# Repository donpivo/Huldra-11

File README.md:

Description: https://retronics.no/tag/huldra11/

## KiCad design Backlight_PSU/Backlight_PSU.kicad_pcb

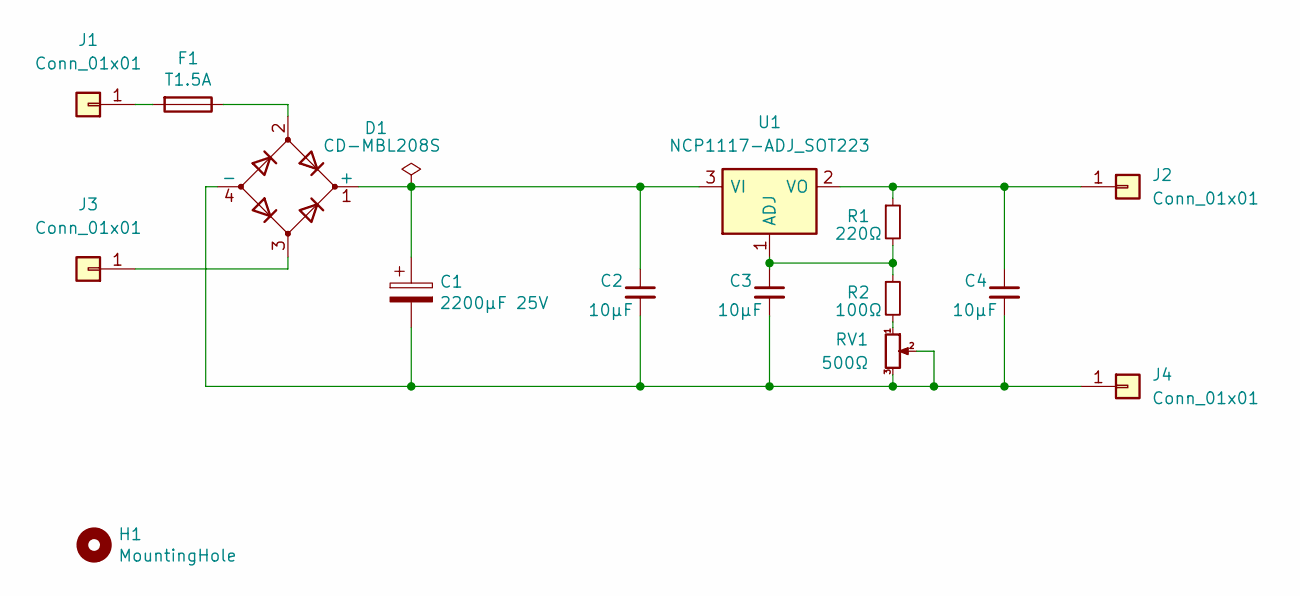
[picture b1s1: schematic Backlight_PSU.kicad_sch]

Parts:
C1: 2200µF 25V; CP_Elec_16x17.5
C2, C3, C4: 10µF; C_0603_1608Metric_Pad1.08x0.95mm_HandSolder
D1: CD-MBL208S; CDMBL208S
F1: T1.5A; Fuse_1206_3216Metric_Pad1.42x1.75mm_HandSolder
H1: MountingHole; MountingHole_3.7mm
J1, J2, J3, J4: Conn_01x01; TestPoint_Pad_2.5x2.5mm
R1: 220Ω; R_0603_1608Metric_Pad0.98x0.95mm_HandSolder
R2: 100Ω; R_0603_1608Metric_Pad0.98x0.95mm_HandSolder
RV1: 500Ω; Potentiometer_Bourns_TC33X_Vertical
U1: NCP1117-ADJ_SOT223; SOT-223-3_TabPin2

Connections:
unnamed: C1.1, C2.1, D1.1 (+), U1.3 (VI)
unnamed: C1.2, C2.2, C3.2, C4.2, D1.4 (-), J4.1, RV1.2, RV1.3
unnamed: D1.2, F1.1
unnamed: F1.2, J1.1
unnamed: C4.1, J2.1, R1.1, U1.2 (VO)
unnamed: D1.3, J3.1
unnamed: R2.2, RV1.1
unnamed: C3.1, R1.2, R2.1, U1.1 (ADJ)

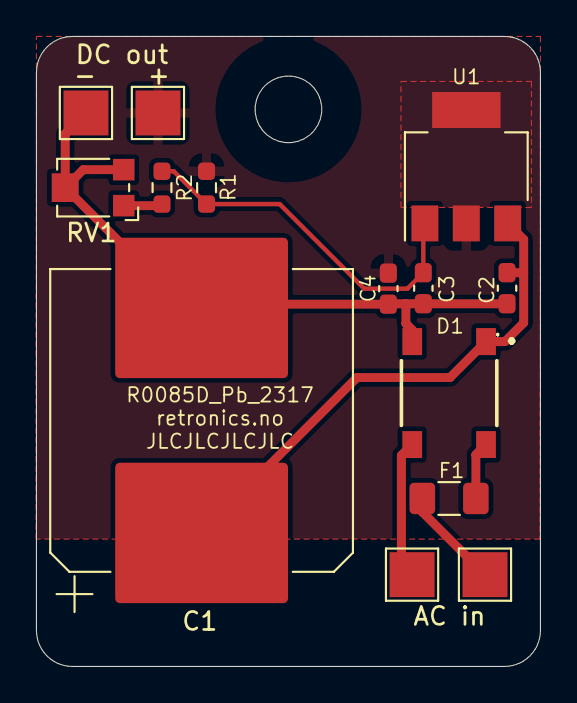
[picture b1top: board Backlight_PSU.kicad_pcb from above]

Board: 2 copper layers, 28.0 x 35.0 mm, 15 parts (0 on the bottom side), 8 nets.

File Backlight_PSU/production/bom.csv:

Designator,Footprint,Quantity,Value,LCSC Part #
C1,CP_Elec_16x17.5,1,2200µF 25V,
"C2, C3, C4",0603,3,10µF,
D1,CDMBL208S,1,CD-MBL208S,
F1,1206,1,T1.5A,
H1,MountingHole_3.7mm,1,MountingHole,
"J1, J2, J3, J4",TestPoint_Pad_2.5x2.5mm,4,Conn_01x01,
R1,0603,1,220Ω,
R2,0603,1,100Ω,
RV1,Potentiometer_Bourns_TC33X_Vertical,1,500Ω,
U1,SOT-223-3_TabPin2,1,NCP1117-ADJ_SOT223,

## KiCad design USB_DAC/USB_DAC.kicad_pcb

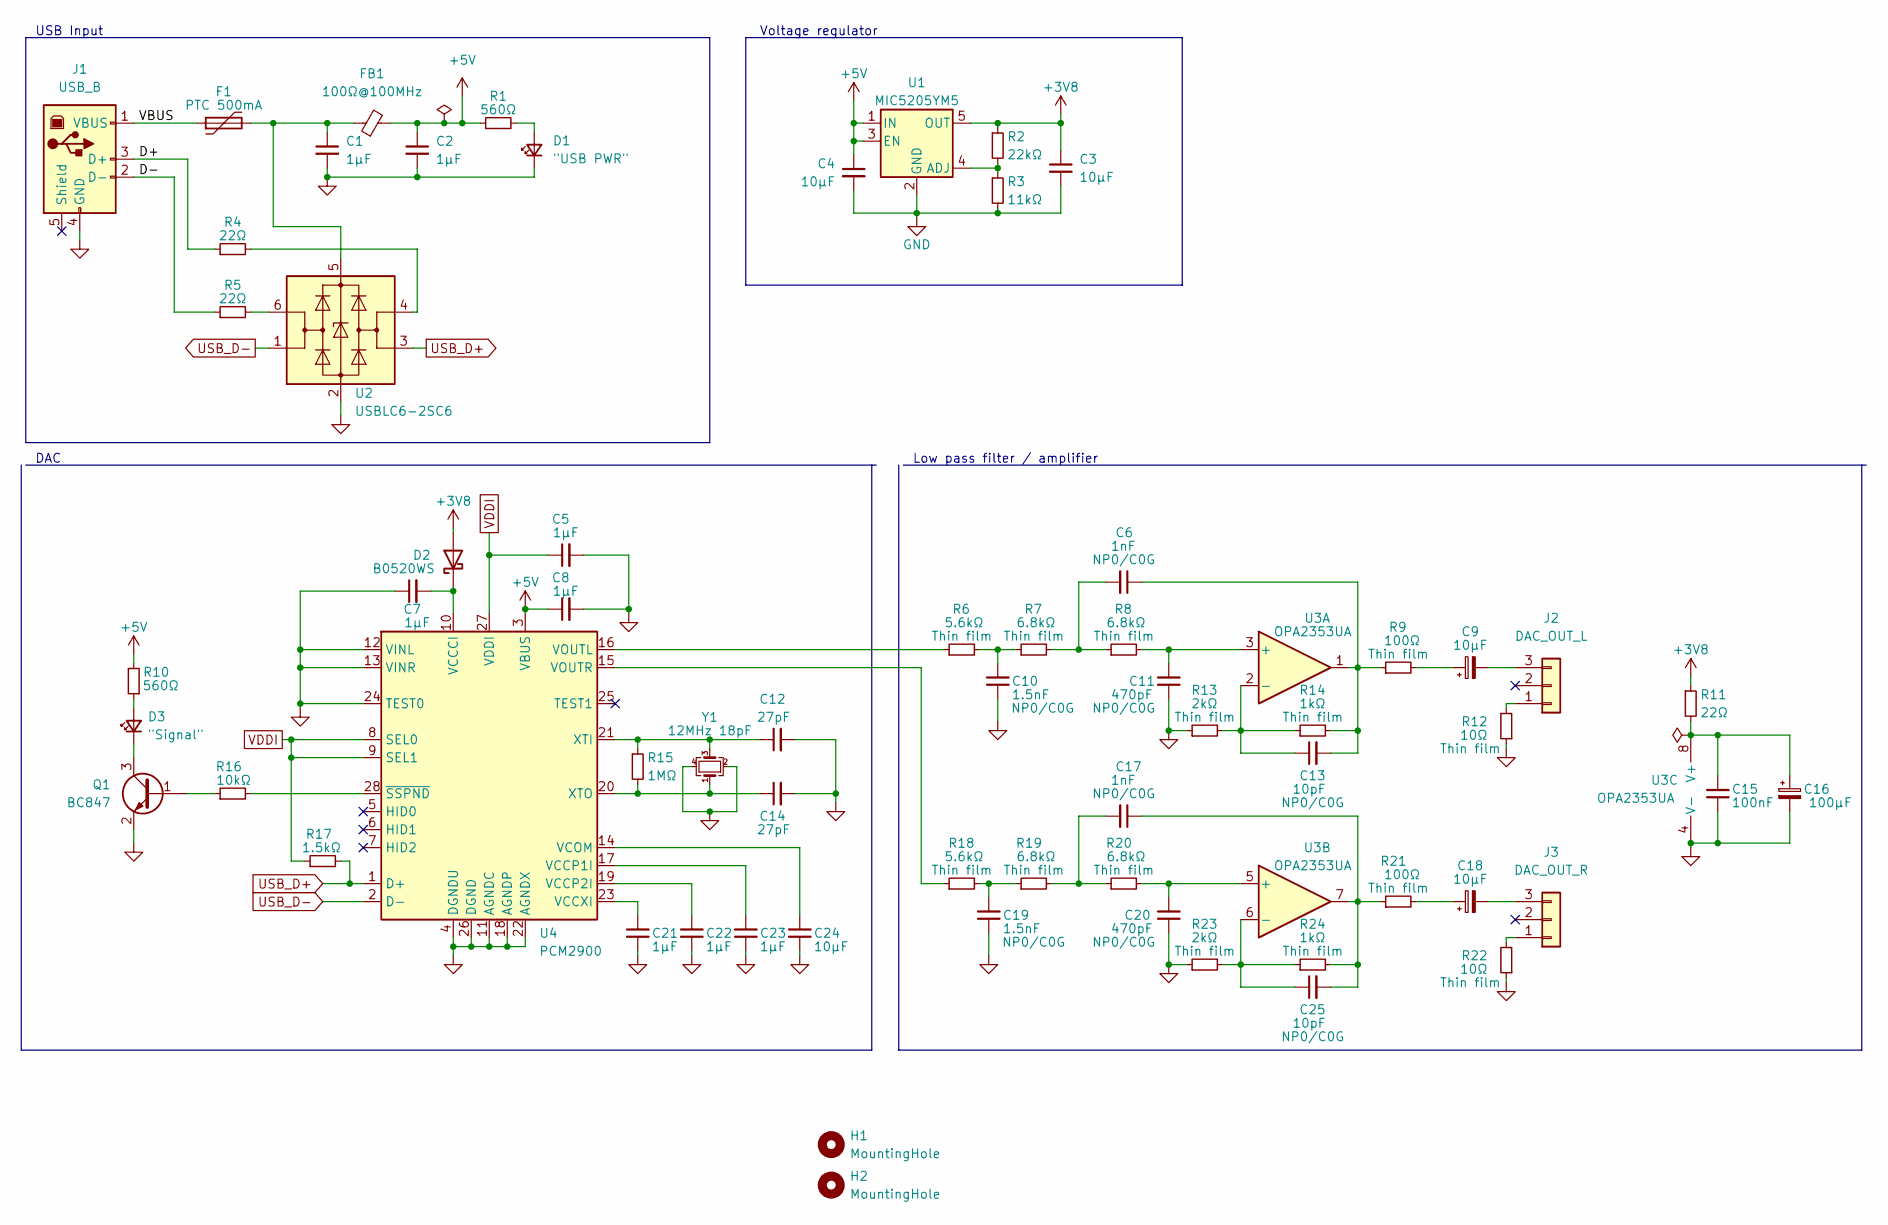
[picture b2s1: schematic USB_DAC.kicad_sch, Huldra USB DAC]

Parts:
C1, C2, C5, C7, C8, C21, C22, C23: 1µF; C_0603_1608Metric_Pad1.08x0.95mm_HandSolder
C3, C4, C24: 10µF; C_0603_1608Metric_Pad1.08x0.95mm_HandSolder
C6, C17: 1nF; C_0603_1608Metric_Pad1.08x0.95mm_HandSolder
C9, C18: 10µF; CP_Radial_D5.0mm_P2.00mm
C10, C19: 1.5nF; C_0603_1608Metric_Pad1.08x0.95mm_HandSolder
C11, C20: 470pF; C_0603_1608Metric_Pad1.08x0.95mm_HandSolder
C12, C14: 27pF; C_0603_1608Metric_Pad1.08x0.95mm_HandSolder
C13, C25: 10pF; C_0603_1608Metric_Pad1.08x0.95mm_HandSolder
C15: 100nF; C_0603_1608Metric_Pad1.08x0.95mm_HandSolder
C16: 100µF; CP_Radial_D5.0mm_P2.00mm
D1: "USB PWR"; LED_0603_1608Metric_Pad1.05x0.95mm_HandSolder
D2: B0520WS; D_SOD-323_HandSoldering
D3: "Signal"; LED_0603_1608Metric_Pad1.05x0.95mm_HandSolder
F1: PTC 500mA; Fuse_0805_2012Metric_Pad1.15x1.40mm_HandSolder
FB1: 100Ω@100MHz; L_0603_1608Metric_Pad1.05x0.95mm_HandSolder
H1, H2: MountingHole; MountingHole_3.2mm_M3
J1: USB_B; 292304
J2: DAC_OUT_L; KF2510-3P
J3: DAC_OUT_R; KF2510-3P
Q1: BC847; SOT-23
R1, R10: 560Ω; R_0603_1608Metric_Pad0.98x0.95mm_HandSolder
R2: 22kΩ; R_0603_1608Metric_Pad0.98x0.95mm_HandSolder
R3: 11kΩ; R_0603_1608Metric_Pad0.98x0.95mm_HandSolder
R4, R5, R11: 22Ω; R_0603_1608Metric_Pad0.98x0.95mm_HandSolder
R6, R18: 5.6kΩ; R_0603_1608Metric_Pad0.98x0.95mm_HandSolder
R7, R8, R19, R20: 6.8kΩ; R_0603_1608Metric_Pad0.98x0.95mm_HandSolder
R9, R21: 100Ω; R_0603_1608Metric_Pad0.98x0.95mm_HandSolder
R12, R22: 10Ω; R_0603_1608Metric_Pad0.98x0.95mm_HandSolder
R13, R23: 2kΩ; R_0603_1608Metric_Pad0.98x0.95mm_HandSolder
R14, R24: 1kΩ; R_0603_1608Metric_Pad0.98x0.95mm_HandSolder
R15: 1MΩ; R_0603_1608Metric_Pad0.98x0.95mm_HandSolder
R16: 10kΩ; R_0603_1608Metric_Pad0.98x0.95mm_HandSolder
R17: 1.5kΩ; R_0603_1608Metric_Pad0.98x0.95mm_HandSolder
U1: MIC5205YM5; SOT-23-5
U2: USBLC6-2SC6; SOT-23-6
U3: OPA2353UA; SOIC-8_3.9x4.9mm_P1.27mm
U4: PCM2900; SSOP-28_5.3x10.2mm_P0.65mm
Y1: 12MHz 18pF; Crystal_SMD_3225-4Pin_3.2x2.5mm_HandSoldering

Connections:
+3V8: C3.1, D2.2 (A), R2.1, R11.1, U1.5 (OUT)
+5V: C2.1, C4.1, C8.1, FB1.2, R1.1, R10.2, U1.1 (IN), U1.3 (EN), U4.3 (VBUS)
/D+: J1.3 (D+), R4.1
/D-: J1.2 (D-), R5.1
/VBUS: F1.1, J1.1 (VBUS)
GND: C1.2, C2.2, C3.2, C4.2, C5.2, C7.1, C8.2, C10.1, C11.1, C12.2, C14.2, C15.1, C16.2, C19.1, C20.1, C21.1, C22.1, C23.1, C24.1, D1.1 (K), J1.4 (GND), Q1.2 (E), R3.2, R12.1, R13.1, R22.1, R23.1, U1.2 (GND), U2.2 (GND), U3.4 (V-), U4.4 (DGNDU), U4.11 (AGNDC), U4.12 (VINL), U4.13 (VINR), U4.18 (AGNDP), U4.22 (AGNDX), U4.24 (TEST0), U4.26 (DGND), Y1.2, Y1.4
unnamed: C6.2, R7.2, R8.1
unnamed: C9.1, R9.2
unnamed: C10.2, R6.2, R7.1
unnamed: C6.1, C13.2, R9.1, R14.2, U3.1
unnamed: C17.1, C25.2, R21.1, R24.2, U3.7
unnamed: C17.2, R19.2, R20.1
unnamed: C18.1, R21.2
unnamed: C19.2, R18.2, R19.1
unnamed: D1.2 (A), R1.2
unnamed: C7.2, D2.1 (K), U4.10 (VCCCI)
unnamed: D3.2 (A), R10.1
unnamed: D3.1 (K), Q1.3 (C)
unnamed: J2.1, R12.2
unnamed: C9.2, J2.3
unnamed: J3.1, R22.2
unnamed: C18.2, J3.3
unnamed: Q1.1 (B), R16.1
unnamed: R4.2, U2.4 (I/O2)
unnamed: R5.2, U2.6 (I/O1)
unnamed: R2.2, R3.1, U1.4 (ADJ)
unnamed: C1.1, F1.2, FB1.1, U2.5 (VBUS)
unnamed: C11.2, R8.2, U3.3 (+)
unnamed: C13.1, R13.2, R14.1, U3.2 (-)
unnamed: C20.2, R20.2, U3.5 (+)
unnamed: C25.1, R23.2, R24.1, U3.6 (-)
unnamed: C15.2, C16.1, R11.2, U3.8 (V+)
unnamed: C23.2, U4.17 (VCCP1I)
unnamed: C22.2, U4.19 (VCCP2I)
unnamed: C21.2, U4.23 (VCCXI)
unnamed: C24.2, U4.14 (VCOM)
unnamed: R6.1, U4.16 (VOUTL)
unnamed: R18.1, U4.15 (VOUTR)
unnamed: C12.1, R15.1, U4.21 (XTI), Y1.3
unnamed: C14.1, R15.2, U4.20 (XTO), Y1.1
unnamed: R16.2, U4.28 (~SSPND)
USB_D+: R17.2, U2.3 (I/O2), U4.1 (D+)
USB_D-: U2.1 (I/O1), U4.2 (D-)
VDDI: C5.1, R17.1, U4.8 (SEL0), U4.9 (SEL1), U4.27 (VDDI)

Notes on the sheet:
Voltage regulator
Low pass filter / amplifier
DAC
USB Input

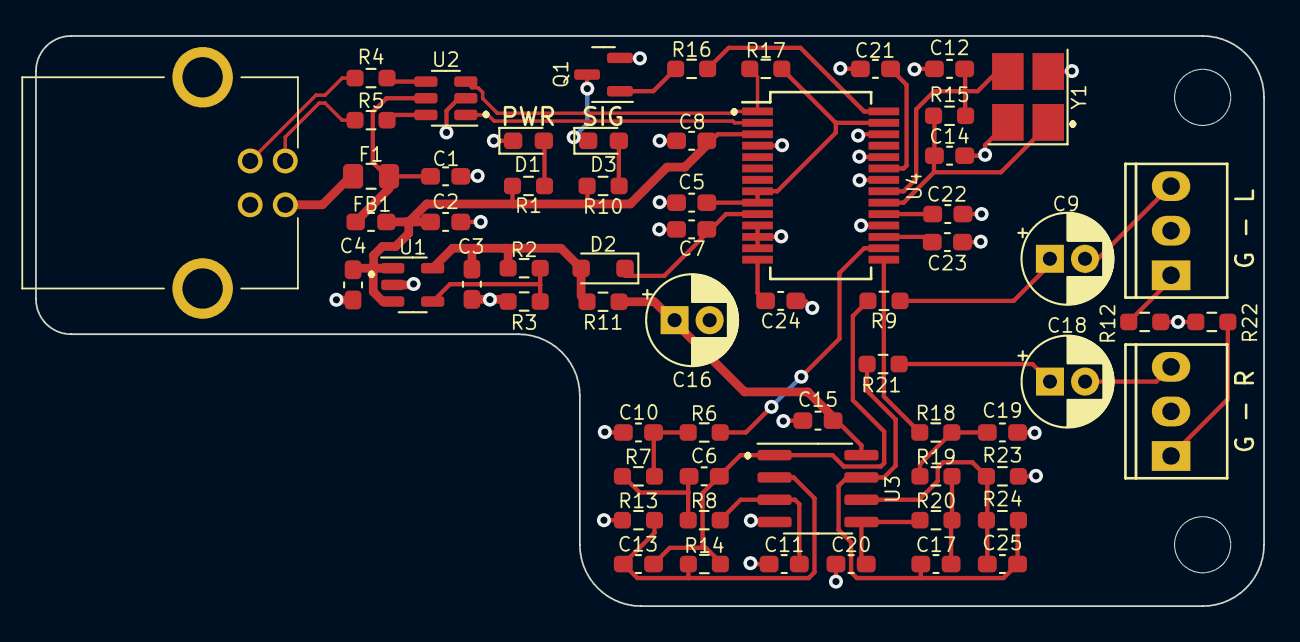
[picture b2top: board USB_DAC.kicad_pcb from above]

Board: 2 copper layers, 70.0 x 32.5 mm, 65 parts (0 on the bottom side), 44 nets.

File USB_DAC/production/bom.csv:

Designator,Footprint,Quantity,Value,LCSC Part #
"C1, C2, C21, C22, C23, C5, C7, C8",0603,8,1µF,
"C10, C19",0603,2,1.5nF,
"C11, C20",0603,2,470pF,
"C12, C14",0603,2,27pF,
"C13, C25",0603,2,10pF,
C15,0603,1,100nF,
C16,CP_Radial_D5.0mm_P2.00mm,1,100µF,
"C17, C6",0603,2,1nF,
"C18, C9",CP_Radial_D5.0mm_P2.00mm,2,10µF,
"C24, C3, C4",0603,3,10µF,
D1,0603,1,"""USB PWR""",
D2,D_SOD-323_HandSoldering,1,B0520WS,
D3,0603,1,"""Signal""",
F1,0805,1,PTC 500mA,
FB1,0603,1,100Ω@100MHz,
"H1, H2",MountingHole_3.2mm_M3,2,MountingHole,
J1,292304,1,USB_B,
J2,KF2510-3P,1,DAC_OUT_L,
J3,KF2510-3P,1,DAC_OUT_R,
Q1,SOT-23,1,BC847,
"R1, R10",0603,2,560Ω,
"R11, R4, R5",0603,3,22Ω,
"R12, R22",0603,2,10Ω,
"R13, R23",0603,2,2kΩ,
"R14, R24",0603,2,1kΩ,
R15,0603,1,1MΩ,
R16,0603,1,10kΩ,
R17,0603,1,1.5kΩ,
"R18, R6",0603,2,5.6kΩ,
"R19, R20, R7, R8",0603,4,6.8kΩ,
R2,0603,1,22kΩ,
"R21, R9",0603,2,100Ω,
R3,0603,1,11kΩ,
U1,SOT-23-5,1,MIC5205YM5,
U2,SOT-23-6,1,USBLC6-2SC6,
U3,SOIC-8_3.9x4.9mm_P1.27mm,1,OPA2353UA,
U4,SSOP-28_5.3x10.2mm_P0.65mm,1,PCM2900,
Y1,Crystal_SMD_3225-4Pin_3.2x2.5mm_HandSoldering,1,12MHz 18pF,

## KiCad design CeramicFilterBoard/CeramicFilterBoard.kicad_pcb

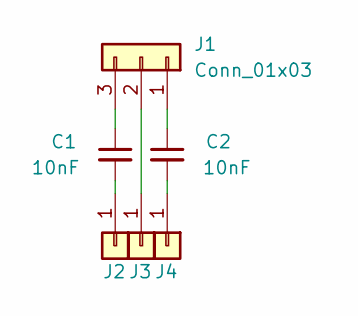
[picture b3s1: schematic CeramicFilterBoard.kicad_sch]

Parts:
C1, C2: 10nF; C_0805_2012Metric
J1: Conn_01x03; Murata_Ceramic_Filter
J2, J3, J4: Conn_01x01; PinHeader_1x01_P2.54mm_Vertical

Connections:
unnamed: C1.1, J1.3
unnamed: C1.2, J2.1
unnamed: C2.1, J1.1
unnamed: C2.2, J4.1
unnamed: J1.2, J3.1

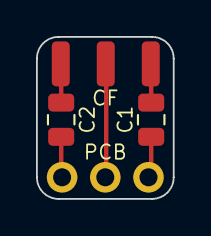
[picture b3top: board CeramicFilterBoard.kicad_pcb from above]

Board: 2 copper layers, 7.6 x 9.0 mm, 6 parts (0 on the bottom side), 5 nets.

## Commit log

2023-04-30 Changed capacitor footprint
2023-04-30 Minor silkscreen update
2023-04-30 Changed capacitor values
2023-04-30 Feedback resistors changed for 0dB gain
2023-05-01 Changed fill zone
2023-05-20 Changed component values
2023-05-21 Updated component values
2023-06-18 File cleanup
